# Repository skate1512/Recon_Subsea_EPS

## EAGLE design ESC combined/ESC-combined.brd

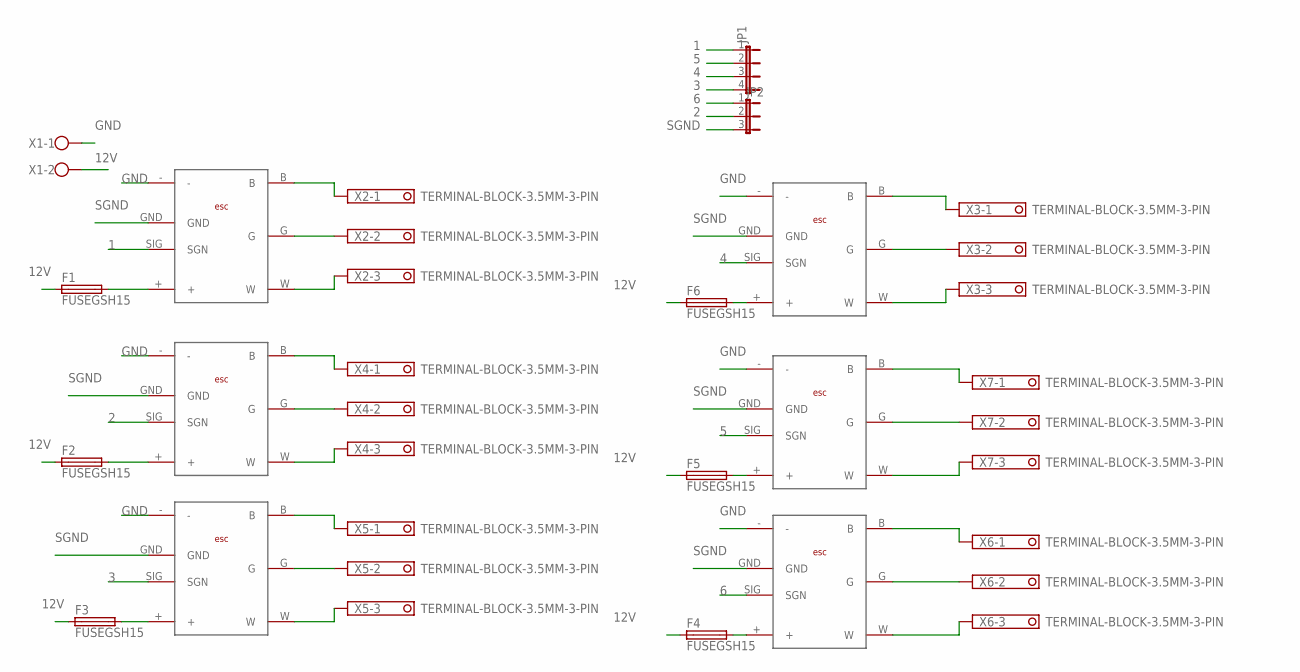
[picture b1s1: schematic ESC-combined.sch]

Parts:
F1, F2, F3, F4, F5, F6: FUSEGSH15; GSH15
JP1: JP4E; JP4
JP2: JP2E; JP2
U$1, U$2, U$3, U$4, U$5, U$6: ESCV!
X1: 12V; W237-102
X2, X3, X4, X5, X6, X7: TERMINAL-BLOCK-3.5MM-3-PIN; HDRV3W150P950_1X3_3150X1470X1860A

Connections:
1: JP1.1, U$1.SIG (SGN)
2: JP2.2, U$2.SIG (SGN)
3: JP1.4, U$3.SIG (SGN)
4: JP1.3, U$4.SIG (SGN)
5: JP1.2, U$5.SIG (SGN)
6: JP2.1, U$6.SIG (SGN)
12V: F1.1, F2.1, F3.1, F4.1, F5.1, F6.1, X1.2
GND: U$1.-, U$2.-, U$3.-, U$4.-, U$5.-, U$6.-, X1.1
unnamed: F6.2, U$4.+
unnamed: F1.2, U$1.+
unnamed: F2.2, U$2.+
unnamed: F3.2, U$3.+
unnamed: F5.2, U$5.+
unnamed: F4.2, U$6.+
unnamed: U$1.B, X2.1
unnamed: U$1.G, X2.2
unnamed: U$1.W, X2.3
unnamed: U$2.B, X4.1
unnamed: U$2.G, X4.2
unnamed: U$2.W, X4.3
unnamed: U$3.B, X5.1
unnamed: U$3.G, X5.2
unnamed: U$3.W, X5.3
unnamed: U$6.B, X6.1
unnamed: U$6.G, X6.2
unnamed: U$6.W, X6.3
unnamed: U$5.B, X7.1
unnamed: U$5.G, X7.2
unnamed: U$5.W, X7.3
unnamed: U$4.B, X3.1
unnamed: U$4.G, X3.2
unnamed: U$4.W, X3.3
SGND: JP2.3, U$1.GND, U$2.GND, U$3.GND, U$4.GND, U$5.GND, U$6.GND

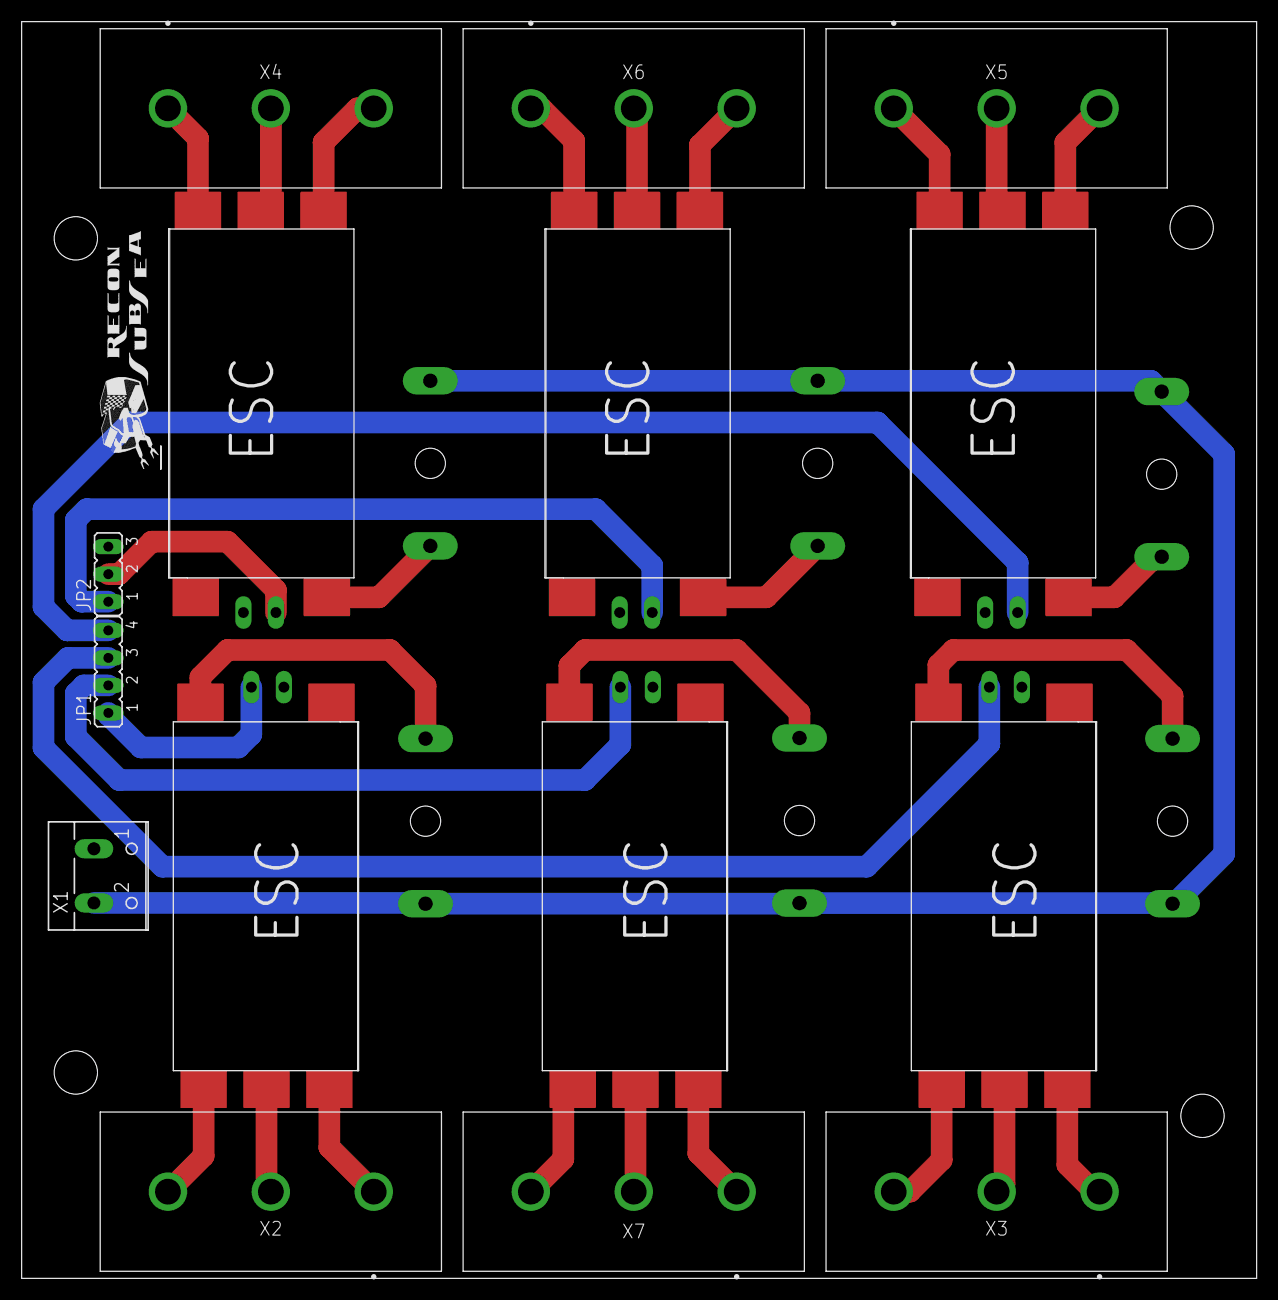
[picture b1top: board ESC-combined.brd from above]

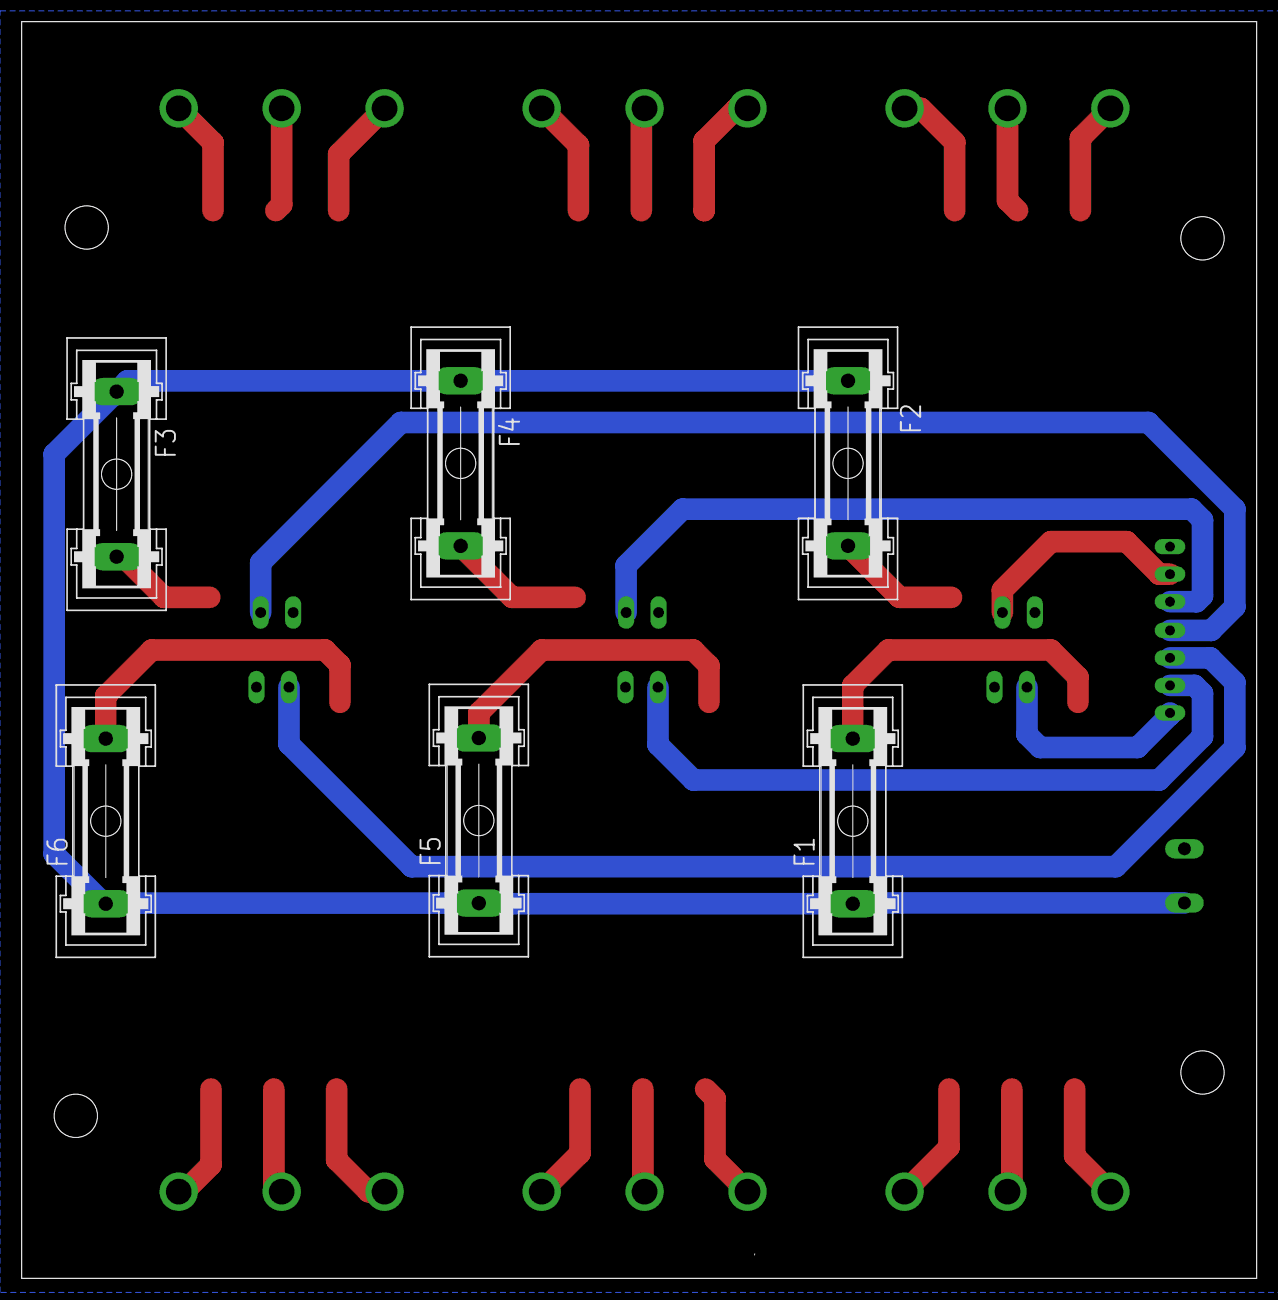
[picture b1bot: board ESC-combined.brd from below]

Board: 2 copper layers, 114.0 x 116.0 mm, 21 parts (6 on the bottom side), 33 nets.

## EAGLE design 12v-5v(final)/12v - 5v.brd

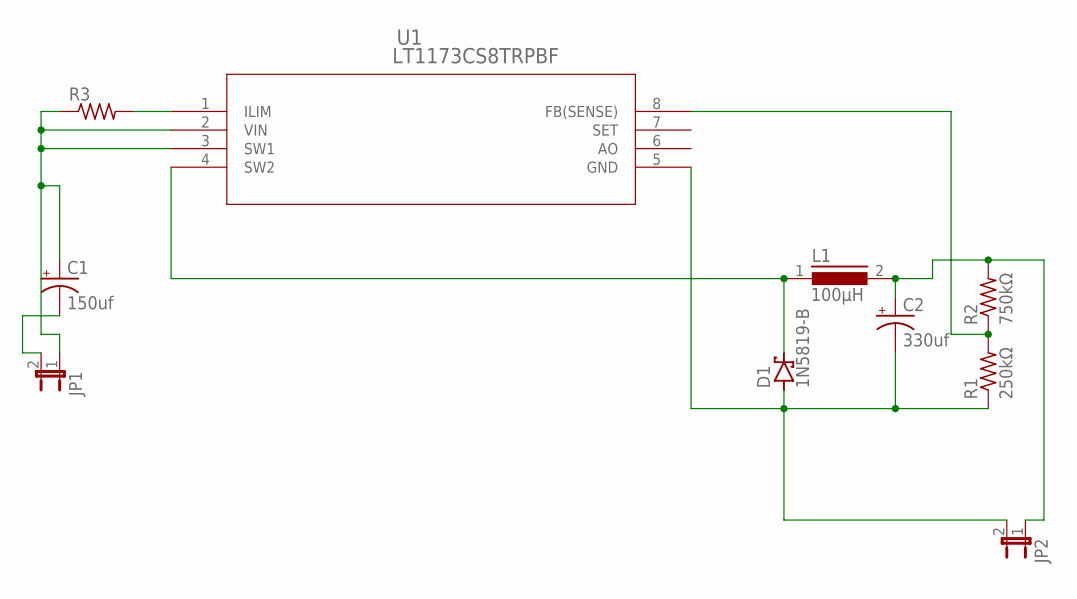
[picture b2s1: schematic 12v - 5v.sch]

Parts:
C1: 150uf; E2-5
C2: 330uf; E2-5
D1: 1N5819-B; DO41-7.6
JP1, JP2: JP1E; JP1
L1: 100μH; S11-10
R1: 250kΩ; 0204/7
R2: 750kΩ; 0204/7
R3: R-US_0204/7; 0204/7
U1: LT1173CS8TRPBF; SOIC-8_S

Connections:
unnamed: R3.2, U1.1 (ILIM)
unnamed: D1.C, L1.1, U1.4 (SW2)
unnamed: C1.-, JP1.2
unnamed: C2.+, JP2.1, L1.2, R2.2
unnamed: C2.-, D1.A, JP2.2, R1.1, U1.5 (GND)
unnamed: R1.2, R2.1, U1.8 (FB(SENSE))
unnamed: C1.+, JP1.1, R3.1, U1.2 (VIN), U1.3 (SW1)

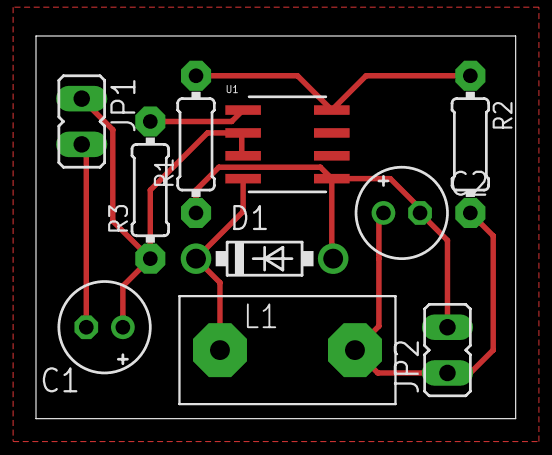
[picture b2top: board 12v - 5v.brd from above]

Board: 2 copper layers, 26.7 x 21.3 mm, 10 parts (0 on the bottom side), 7 nets.

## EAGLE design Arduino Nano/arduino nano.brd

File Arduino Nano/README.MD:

# Arduino Nano 

Arduino Nano board made using Autodesk Eagle.

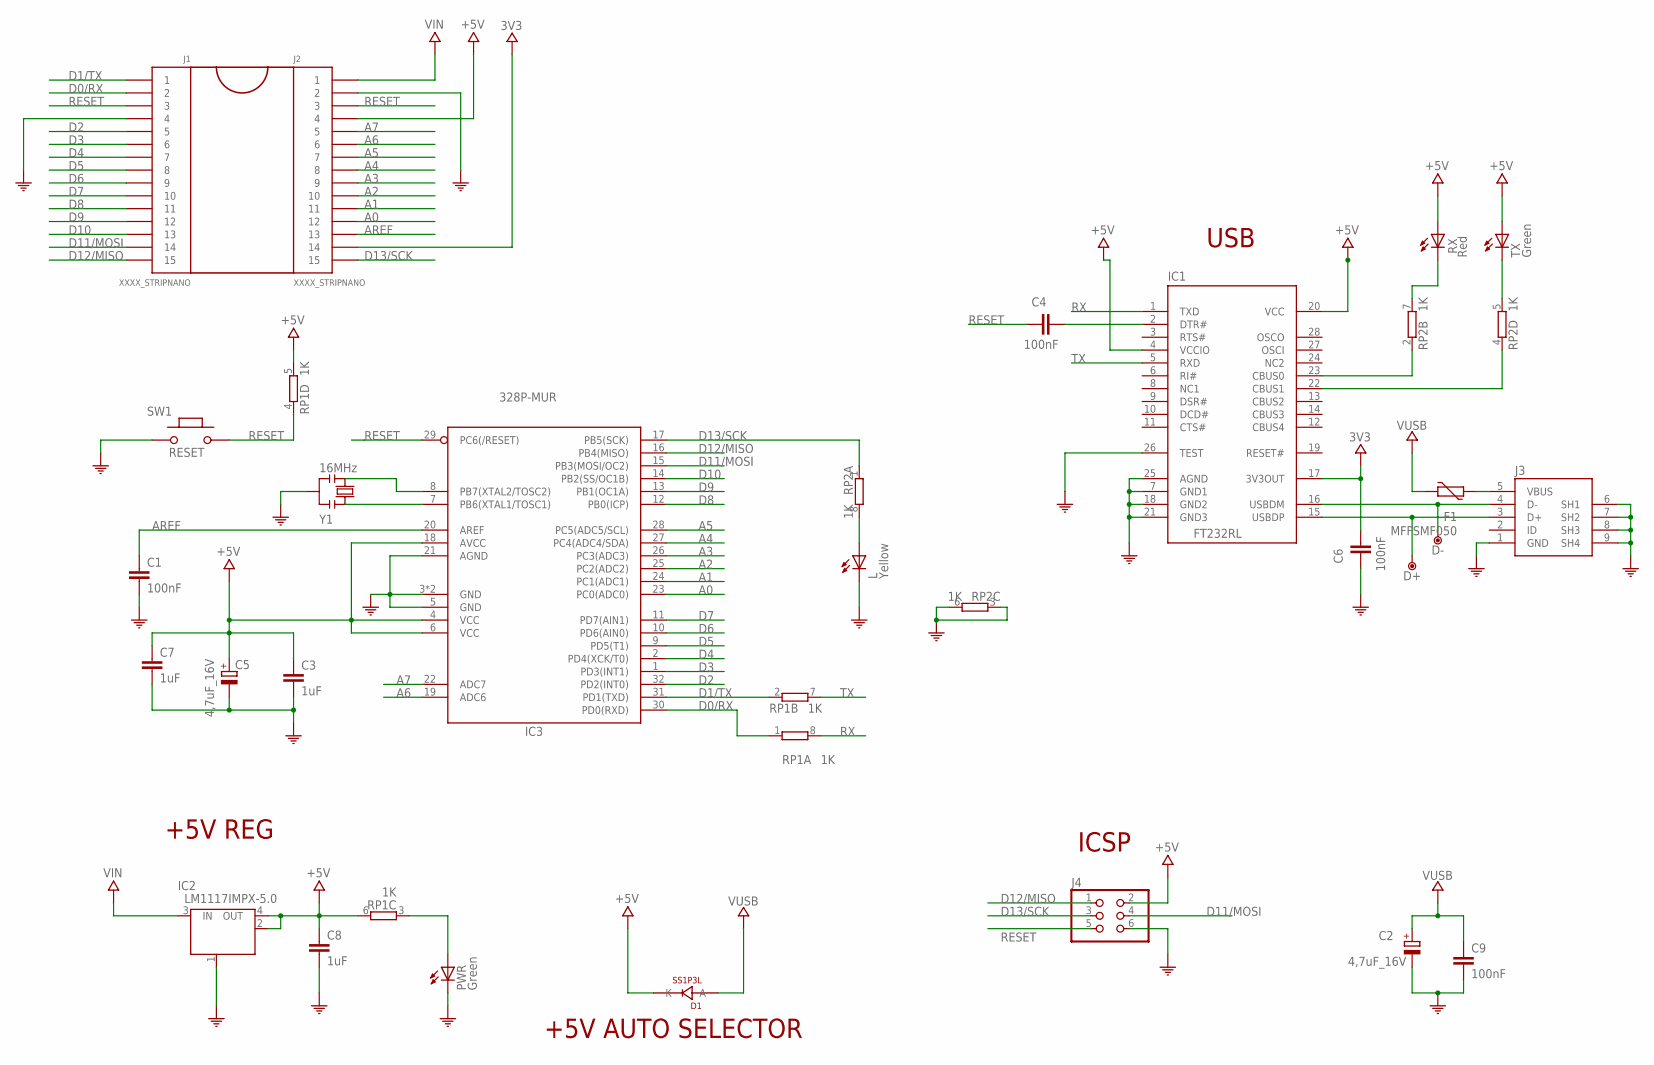
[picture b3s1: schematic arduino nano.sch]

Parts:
C1, C4, C6, C9: 100nF; C0603-ROUND
C2, C5: 4,7uF_16V; TAN-A
C3, C7, C8: 1uF; C0603-ROUND
D1: SS1P3L; DO220AAL
D+: DNP; TP-1.00MM
D-: DNP; TP-1.00MM
F1: MFFSMF050; 0603-1608X90N
IC1: FT232RL; SSOP28
IC2: LM1117IMPX-5.0; LINEAR_SOT223
IC3: 328P-MUR; VQFN32
J1, J2: XXXX_STRIPNANO; HEAD15-NOSS
J3: 0219_14850; USB-MINI-B_2
J4: 0114_PH254-203DF118A00V; 2X03
L: Yellow; CHIPLED_0805
PWR: Green; CHIPLED_0805
RP1, RP2: 1K; CAY16
RX: Red; CHIPLED_0805
SW1: RESET; SMD_157SW
TX: Green; CHIPLED_0805
Y1: 16MHz; RESONATOR

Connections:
3V3: C6.2, IC1.17 (3V3OUT), J2.14
+5V: C3.1, C5.1 (+), C7.1, C8.1, D1.P$1 (K), IC1.4 (VCCIO), IC1.20 (VCC), IC2.2 (OUT), IC2.4 (OUT), IC3.4 (VCC), IC3.6 (VCC), IC3.18 (AVCC), J2.4, J4.2, RP1.5 (2), RP1.6 (2), RX.A, TX.A
A0: IC3.23 (PC0(ADC0)), J2.12
A1: IC3.24 (PC1(ADC1)), J2.11
A2: IC3.25 (PC2(ADC2)), J2.10
A3: IC3.26 (PC3(ADC3)), J2.9
A4: IC3.27 (PC4(ADC4/SDA)), J2.8
A5: IC3.28 (PC5(ADC5/SCL)), J2.7
A6: IC3.19 (ADC6), J2.6
A7: IC3.22 (ADC7), J2.5
AREF: C1.1, IC3.20 (AREF), J2.13
COM: C1.2, C2.2 (-), C3.2, C5.2 (-), C6.1, C7.2, C8.2, C9.2, IC1.7 (GND1), IC1.18 (GND2), IC1.21 (GND3), IC1.25 (AGND), IC1.26 (TEST), IC2.1 (GND/ADJ), IC3.3 (GND), IC3.5 (GND), IC3.21 (AGND), IC3.33 (GND), J1.4, J2.2, J3.1 (GND), J3.6 (SH1), J3.7 (SH2), J3.8 (SH3), J3.9 (SH4), J4.6, L.C, PWR.C, RP2.3 (1), RP2.6 (2), SW1.1, Y1.2
D0/RX: IC3.30 (PD0(RXD)), J1.2, RP1.1
D1/TX: IC3.31 (PD1(TXD)), J1.1, RP1.2 (1)
D2: IC3.32 (PD2(INT0)), J1.5
D3: IC3.1 (PD3(INT1)), J1.6
D4: IC3.2 (PD4(XCK/T0)), J1.7
D5: IC3.9 (PD5(T1)), J1.8
D6: IC3.10 (PD6(AIN0)), J1.9
D7: IC3.11 (PD7(AIN1)), J1.10
D8: IC3.12 (PB0(ICP)), J1.11
D9: IC3.13 (PB1(OC1A)), J1.12
D10: IC3.14 (PB2(SS/OC1B)), J1.13
D11/MOSI: IC3.15 (PB3(MOSI/OC2)), J1.14, J4.4
D12/MISO: IC3.16 (PB4(MISO)), J1.15, J4.1
D13/SCK: IC3.17 (PB5(SCK)), J2.15, J4.3, RP2.1
unnamed: IC1.23 (CBUS0), RP2.2 (1)
unnamed: L.A, RP2.8 (2)
unnamed: D+.X, IC1.15 (USBDP), J3.3 (D+)
unnamed: C4.2, IC1.2 (DTR#)
unnamed: IC3.7 (PB6(XTAL1/TOSC1)), Y1.1
unnamed: IC3.8 (PB7(XTAL2/TOSC2)), Y1.3
unnamed: PWR.A, RP1.3 (1)
unnamed: F1.2, J3.5 (VBUS)
unnamed: D-.X, IC1.16 (USBDM), J3.4 (D-)
unnamed: IC1.22 (CBUS1), RP2.4 (1)
unnamed: RP2.5 (2), TX.C
RESET: C4.1, IC3.29 (PC6(/RESET)), J1.3, J2.3, J4.5, RP1.4 (1), SW1.2
RX: IC1.1 (TXD), RP1.8 (2), RP2.7 (2), RX.C
TX: IC1.5 (RXD), RP1.7 (2)
VIN: IC2.3 (IN), J2.1
VUSB: C2.1 (+), C9.1, D1.P$2 (A), F1.1

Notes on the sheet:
+5V REG
ICSP
USB
+5V AUTO SELECTOR

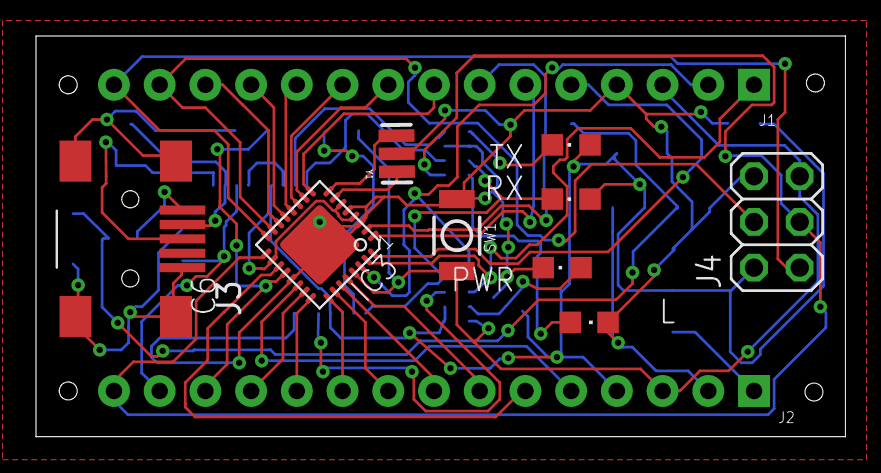
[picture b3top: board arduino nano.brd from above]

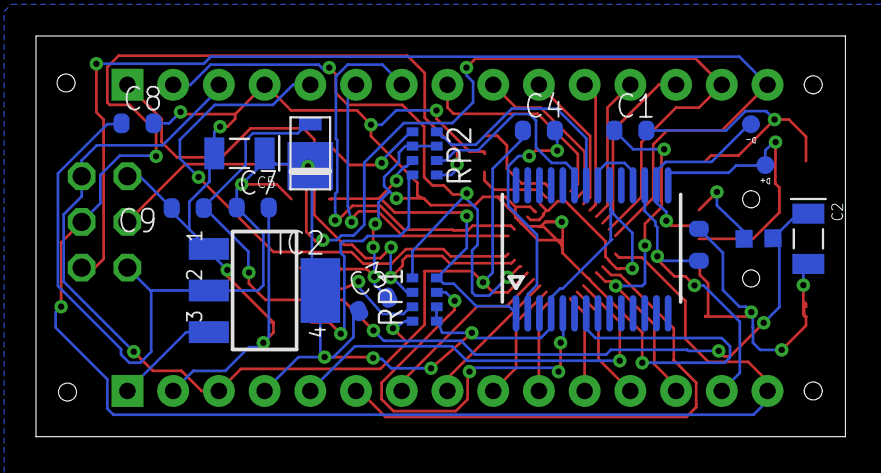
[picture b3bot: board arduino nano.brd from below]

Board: 2 copper layers, 45.0 x 22.3 mm, 28 parts (15 on the bottom side), 42 nets.

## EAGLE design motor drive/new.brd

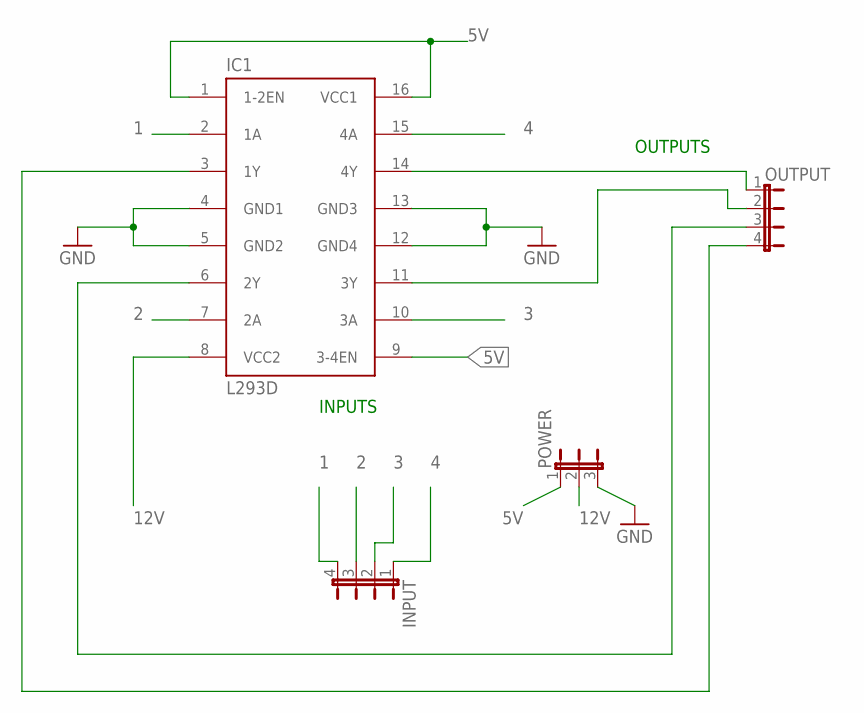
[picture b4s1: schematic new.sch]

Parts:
IC1: L293D; DIL16
INPUT: JP4E; JP4
OUTPUT: JP4E; JP4
POWER: JP2E; JP2

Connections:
1: IC1.2 (1A), INPUT.4
2: IC1.7 (2A), INPUT.3
3: IC1.10 (3A), INPUT.2
4: IC1.15 (4A), INPUT.1
5V: IC1.1 (1-2EN), IC1.9 (3-4EN), IC1.16 (VCC1), POWER.1
12V: IC1.8 (VCC2), POWER.2
GND: IC1.4 (GND1), IC1.5 (GND2), IC1.12 (GND4), IC1.13 (GND3), POWER.3
unnamed: IC1.14 (4Y), OUTPUT.1
unnamed: IC1.11 (3Y), OUTPUT.2
unnamed: IC1.3 (1Y), OUTPUT.4
unnamed: IC1.6 (2Y), OUTPUT.3

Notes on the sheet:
INPUTS
OUTPUTS

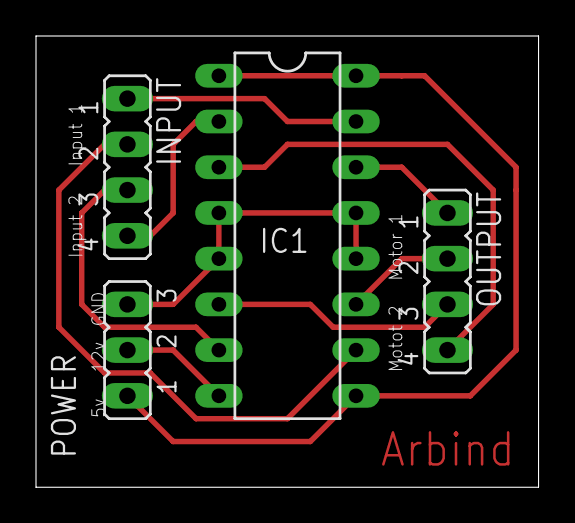
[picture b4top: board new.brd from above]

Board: 2 copper layers, 27.9 x 25.1 mm, 4 parts (0 on the bottom side), 11 nets.

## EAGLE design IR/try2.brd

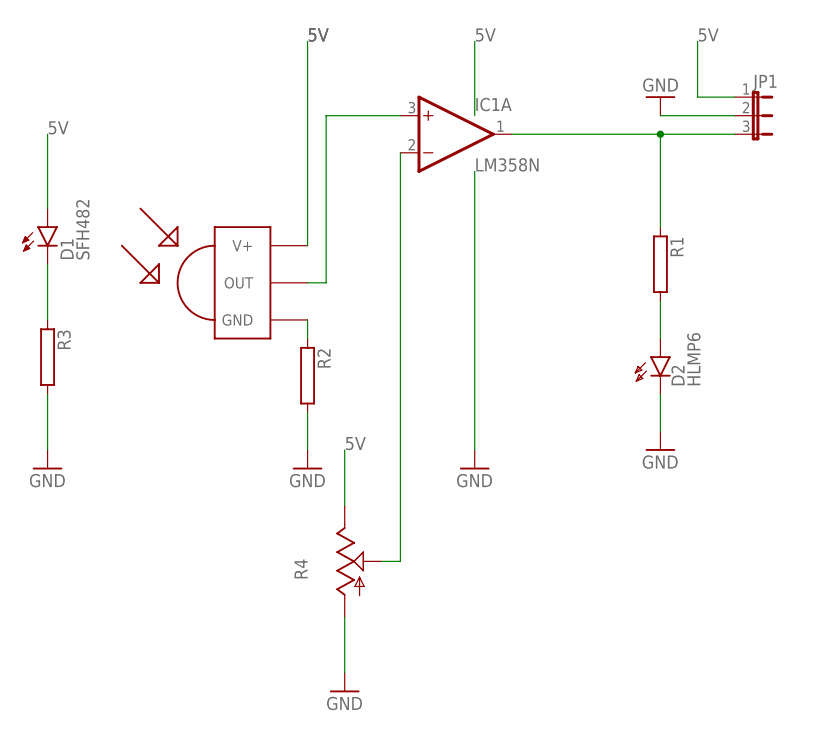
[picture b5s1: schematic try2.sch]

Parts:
D1: SFH482
D2: HLMP6
IC1: LM358N; DIL08
JP1: JP2E; JP2
R1, R2, R3: RAC01; AC01
R4: TRIM_US-CA9H; CA9H
TSOP1: TSOP1730; TSOP17XX

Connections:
5V: D1.A, R4.E, TSOP1.V+
GND: D2.K, JP1.2, R2.2, R3.2, R4.A
unnamed: IC1.2 (-IN), R4.S
unnamed: D2.A, R1.2
unnamed: IC1.1 (OUT), JP1.3, R1.1
unnamed: R2.1, TSOP1.GND
unnamed: IC1.3 (+IN), TSOP1.OUT
unnamed: D1.K (C), R3.1
V+: IC1.8 (V+)
V-: IC1.4 (V-)

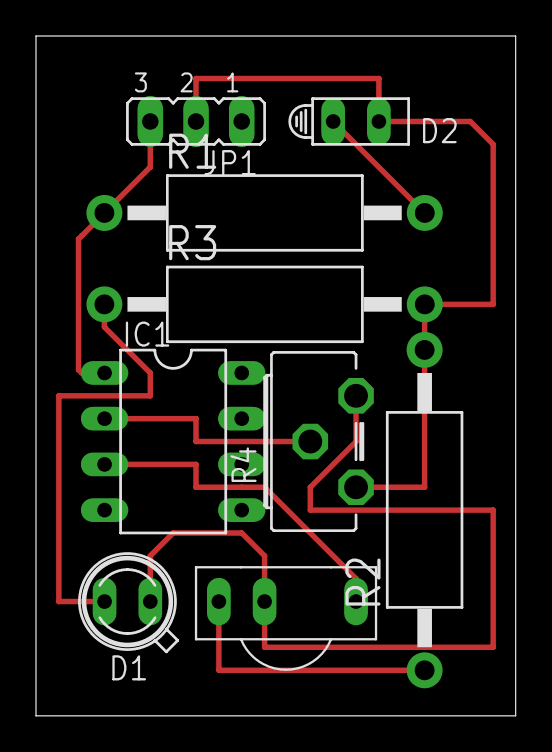
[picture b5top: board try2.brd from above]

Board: 2 copper layers, 26.6 x 37.8 mm, 9 parts (0 on the bottom side), 8 nets.

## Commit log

2020-10-09 Blue Robotics ESC
2021-01-22 ESC Combined PCB

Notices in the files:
parts and their libraries:
Arduino-utility: Copyright (c) 2016-2017 Arduino LLC.  All right reserved.
